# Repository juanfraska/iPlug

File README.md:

# iPlug

This repository will include all codes we using for our iPlug project. You can have a look at the project in the following link: http://www.instructables.com/id/IPlug/ 

In this repo, we have the ESP8266 code, the Node.js server and the PCB files (optional). Also, there are some
current sensor tests.

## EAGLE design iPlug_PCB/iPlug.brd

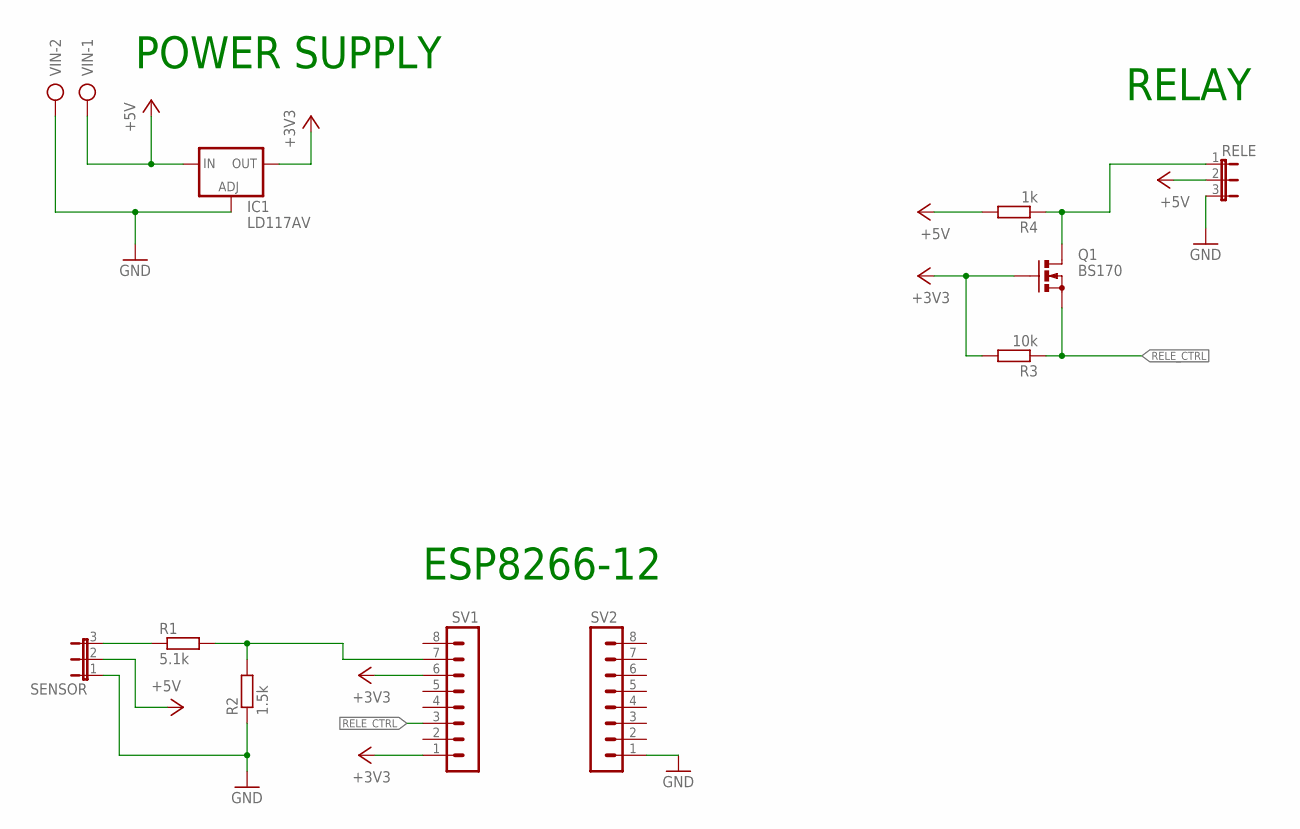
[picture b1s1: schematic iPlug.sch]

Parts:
IC1: LD117AV; TO220L1
Q1: BS170; SOT54E
R1: 5.1k; 0207/10
R2: 1.5k; 0207/10
R3: 10k; 0207/10
R4: 1k; 0207/10
RELE: JP2E; JP2
SENSOR: JP2E; JP2
SV1, SV2: MA08-1
VIN: AK500/2

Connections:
+3V3: IC1.2 (OUT), Q1.G, R3.2, SV1.1, SV1.6
+5V: IC1.3 (IN), R4.2, RELE.2, SENSOR.2, VIN.1
GND: IC1.1 (ADJ), R2.1, RELE.3, SENSOR.1, SV2.1, VIN.2
unnamed: R1.2, R2.2, SV1.7
unnamed: R1.1, SENSOR.3
unnamed: Q1.D, R4.1, RELE.1
RELE_CTRL: Q1.S, R3.1, SV1.3

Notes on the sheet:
ESP8266-12
POWER SUPPLY
RELAY

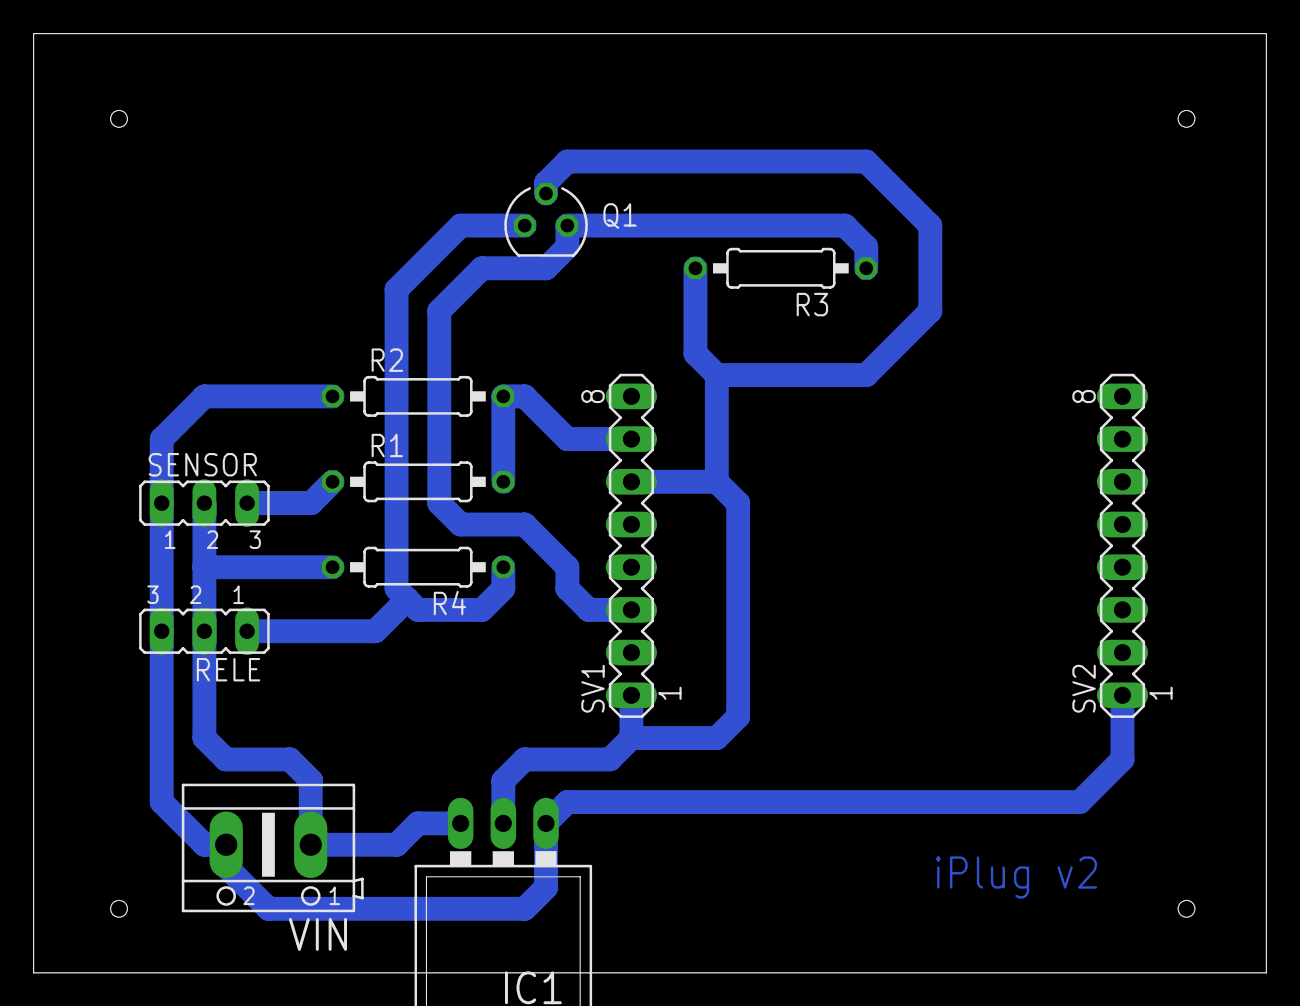
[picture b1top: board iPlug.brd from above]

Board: 2 copper layers, 73.3 x 55.9 mm, 11 parts (0 on the bottom side), 7 nets.

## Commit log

2017-01-31 DC Current code
2017-01-31 AC Current code
2017-01-31 Server code
2017-01-31 Readme #1
2017-02-01 Final code
2017-02-01 Update the server code
2017-02-01 Update the name of the folders
2017-02-01 Correct some code comments
2017-02-01 Upload the PCB files
2017-02-09 Killo que la he liao
2017-02-09 Segundo commit
